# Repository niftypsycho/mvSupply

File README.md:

# mvSupply
 Battery powered linear power supply

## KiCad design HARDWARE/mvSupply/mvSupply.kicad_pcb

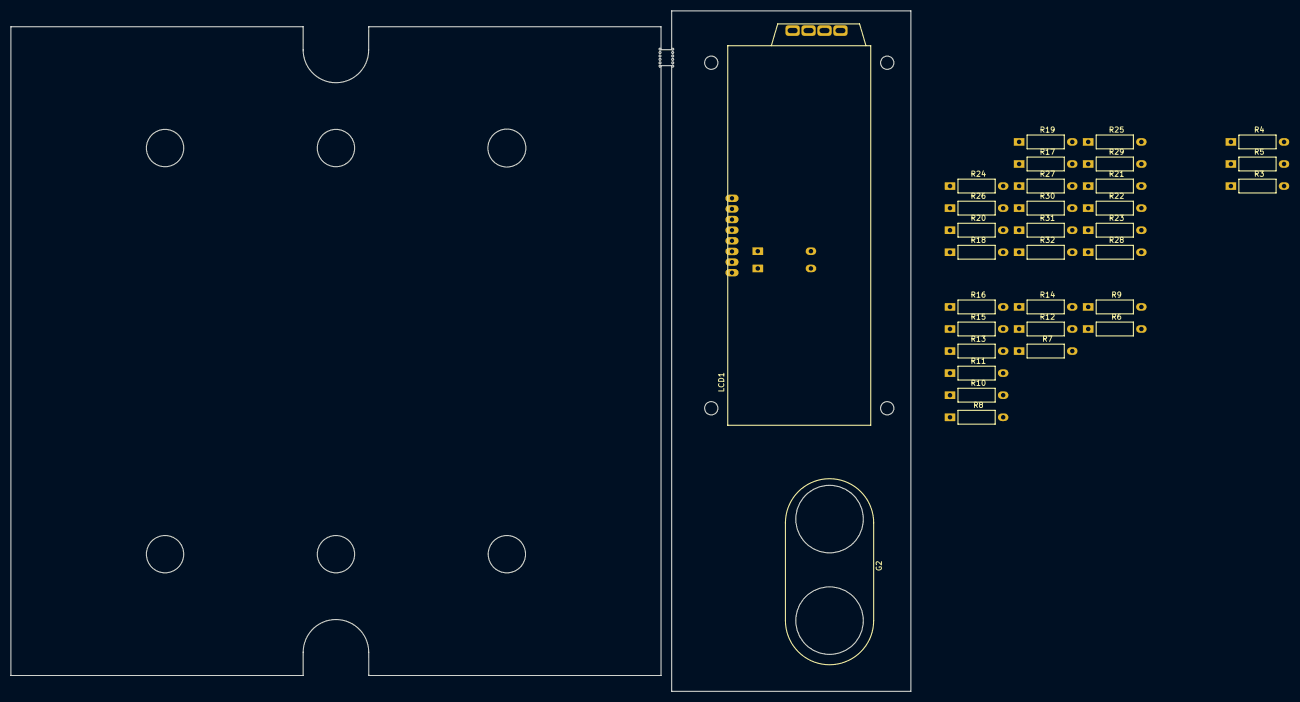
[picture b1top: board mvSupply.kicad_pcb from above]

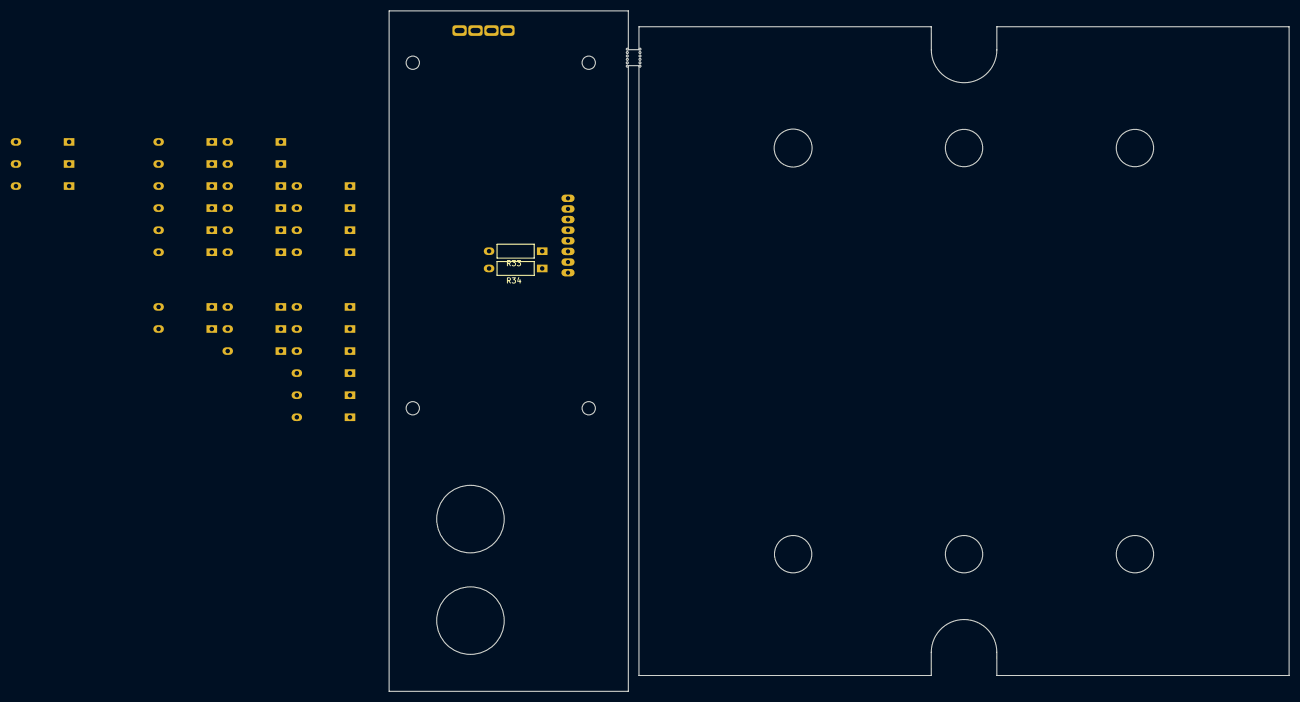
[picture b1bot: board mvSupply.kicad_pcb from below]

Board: 2 copper layers, 169.3 x 128.0 mm, 34 parts (2 on the bottom side), 11 nets, no tracks yet.

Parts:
G2: G; H_BindingPost-Dual
LCD1: LCD_NHD-C0220BIZ-FSRGB-FBW-3VM; NHD-C0220BiZ-FSRGB-FBW-3VM
R3, R4, R5, R6, R7, R8, R9, R10, R11, R12, R13, R14, R15, R16, R17, R18, R19, R20, R21, R22, R23, R24, R25, R26, R27, R28, R29, R30, R31, R32, R33, R34: R; R_AXIAL_L7mm_D2.6mm_P10mm_Horizontal

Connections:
+3V3: LCD1.5 (VDD), R3.2, R5.2, R19.2, R20.2, R21.2, R22.2, R23.2, R24.2, R25.2, R28.2, R33.2, R34.2
+5V: R29.2, R30.2, R31.2, R32.2
/Interface/DISPLAY_SCL: LCD1.2 (SCL), R34.1
/Interface/DISPLAY_SDA: LCD1.3 (SDA), R33.1
unnamed: R6.1, R7.1, R8.1, R9.1, R10.1, R11.1, R12.1, R13.1, R14.1, R15.1
unnamed: R17.1, R19.1
unnamed: R24.1, R26.2
unnamed: R18.1, R20.1
unnamed: R25.1, R27.2
unnamed: R4.1, R5.1
unnamed: R6.2, R7.2, R8.2, R9.2, R10.2, R11.2, R12.2, R13.2, R14.2, R15.2

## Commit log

2022-06-06 Initial commit
    Putting project into GitHub to easily track changes and progress
2022-06-14 Added gitignore
    same as before
2022-06-14 Added submodule
    added submodule
2022-06-14 Delete -gitsubmodules
    Trying from scratch
2022-06-14 Added submodule
    Added master_vampire library correctly
2022-06-14 Testing submodule push
    I modified files in the footprint library. Checking to see if it updates the master-vampire repository on the push
2022-06-14 Update library
    maybe
2022-06-21 Testing submodule retrieval
    Committing to see if it will grab latest library commit
2022-06-21 Standardized directory and library
    Directory is now the same as other hardware projects and points to maintained GitHub library
